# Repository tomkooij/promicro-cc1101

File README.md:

# e07-900m10s adapter board for Arduino Pro Micro (and esp32c3)
Adapter board for [ebyte e07-900m10s CC1101 module](https://www.ebyte.com/en/product-view-news.html?id=1567) and Arduino Pro Micro.

Using [evofw3](https://github.com/ghoti/evofw3) this is an Honeywell HGI-80 clone, that can be used to control Itho/Orcon fans (and evohome devices).
Use the [ramses_cc](https://github.com/zxdavb/ramses_cc) Home Assitant integration.

 - Arduino Pro Micro: mount the reset switch. The RX/TX LEDs are not used: The Pro Micro has on-board leds that are used by evofe3.
 - ESP32-C3: Optionally mount the RX/TX leds. Reset button is on-board. This can run ramses ESP.

TODO (improve in next version):
 - esp32c3 mosi/sclk/miso is reversed as compared my other boards MOSI = 10, SCLK 9... GPO2 5
   (pcb silkscreen is correct)
 - pro micro GND pins next to TX/RX are not connected to pcb GND plane

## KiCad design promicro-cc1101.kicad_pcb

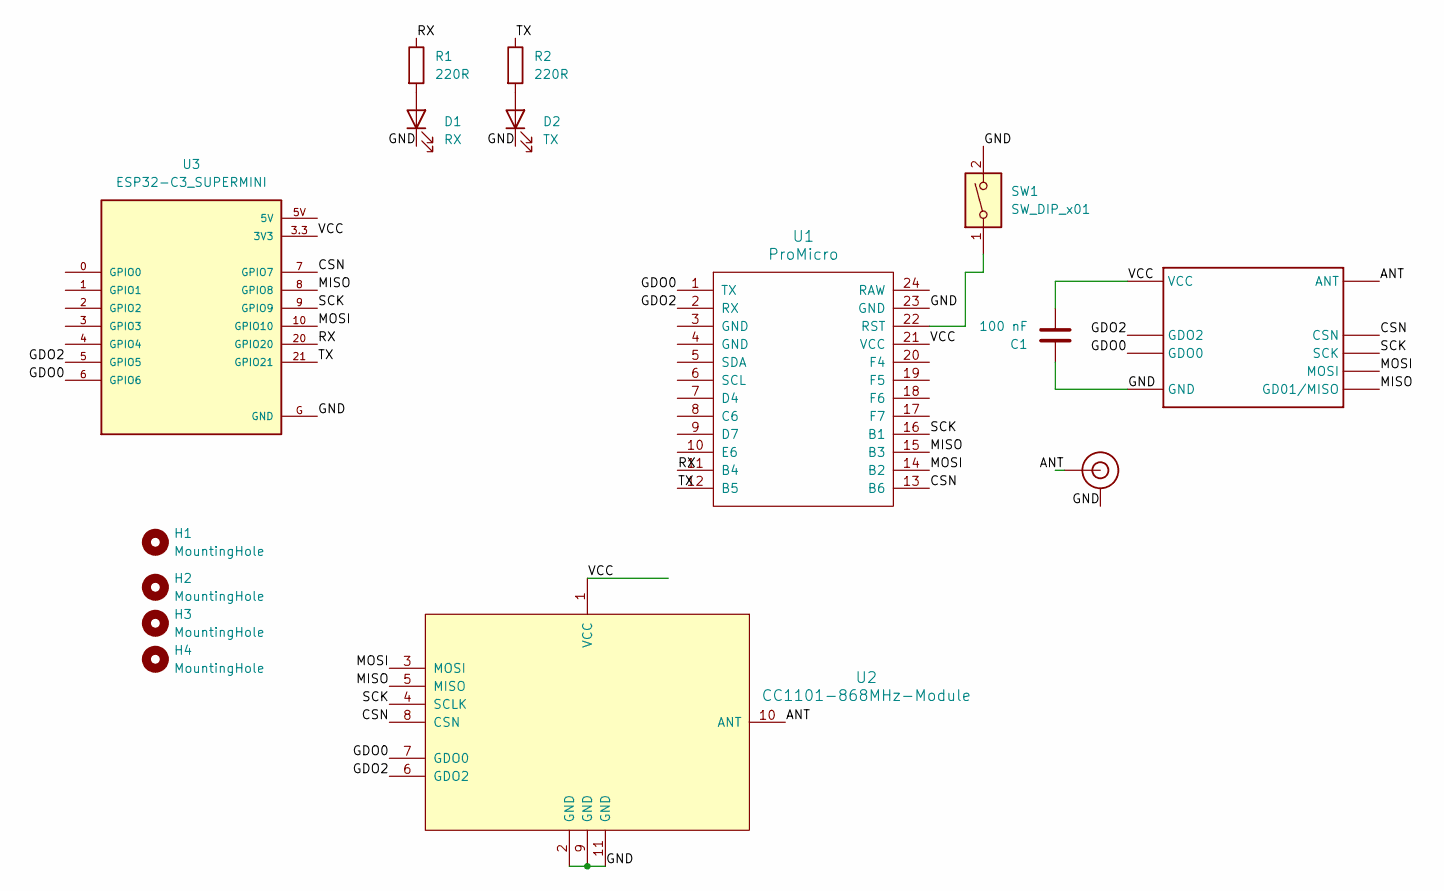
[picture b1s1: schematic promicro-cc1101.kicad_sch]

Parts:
1: E07-900M10S
C1: 100 nF; C_1206_3216Metric_Pad1.33x1.80mm_HandSolder
D1: RX; LED_1206_3216Metric_Pad1.42x1.75mm_HandSolder
D2: TX; LED_1206_3216Metric_Pad1.42x1.75mm_HandSolder
H1, H2, H3, H4: MountingHole; MountingHole_3.2mm_M3
J$1: SMA_PAD
R1, R2: 220R; R_1206_3216Metric_Pad1.30x1.75mm_HandSolder
SW1: SW_DIP_x01; SW_Push_1P1T_NO_CK_KMR2
U1: ProMicro
U2: CC1101-868MHz-Module
U3: ESP32-C3_SUPERMINI; MODULE_ESP32-C3_SUPERMINI

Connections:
/ANT: 1.21 (ANT), J$1.ANT0 (ANT), J$1.ANT1 (ANT), J$1.ANT2 (ANT), U2.10 (ANT)
/CSN: 1.19 (CSN), U1.13 (B6), U2.8 (CSN), U3.7 (GPIO7)
/GDO0: 1.15 (GDO0), U1.1 (TX), U2.7 (GDO0), U3.6 (GPIO6)
/GDO2: 1.14 (GDO2), U1.2 (RX), U2.6 (GDO2), U3.5 (GPIO5)
/GND: 1.1 (GND), 1.2 (GND), 1.3 (GND), 1.4 (GND), 1.5 (GND), 1.11 (GND), 1.12 (GND), 1.20 (GND), 1.22 (GND), C1.1, D1.1 (K), D2.1 (K), J$1.GND3 (GND), J$1.GND4 (GND), J$1.GND5 (GND), J$1.GND6 (GND), SW1.2, U1.23 (GND), U2.2 (GND), U2.9 (GND), U2.11 (GND), U3.G (GND)
/MISO: 1.16 (GD01/MISO), U1.15 (B3), U2.5 (MISO), U3.8 (GPIO8)
/MOSI: 1.17 (MOSI), U1.14 (B2), U2.3 (MOSI), U3.10 (GPIO10)
/RX: R1.1, U1.11 (B4), U3.20 (GPIO20)
/SCK: 1.18 (SCK), U1.16 (B1), U2.4 (SCLK), U3.9 (GPIO9)
/TX: R2.1, U1.12 (B5), U3.21 (GPIO21)
/VCC: 1.9 (VCC), C1.2, U1.21 (VCC), U2.1 (VCC), U3.3.3 (3V3)
unnamed: D1.2 (A), R1.2
unnamed: D2.2 (A), R2.2
unnamed: SW1.1, U1.22 (RST)

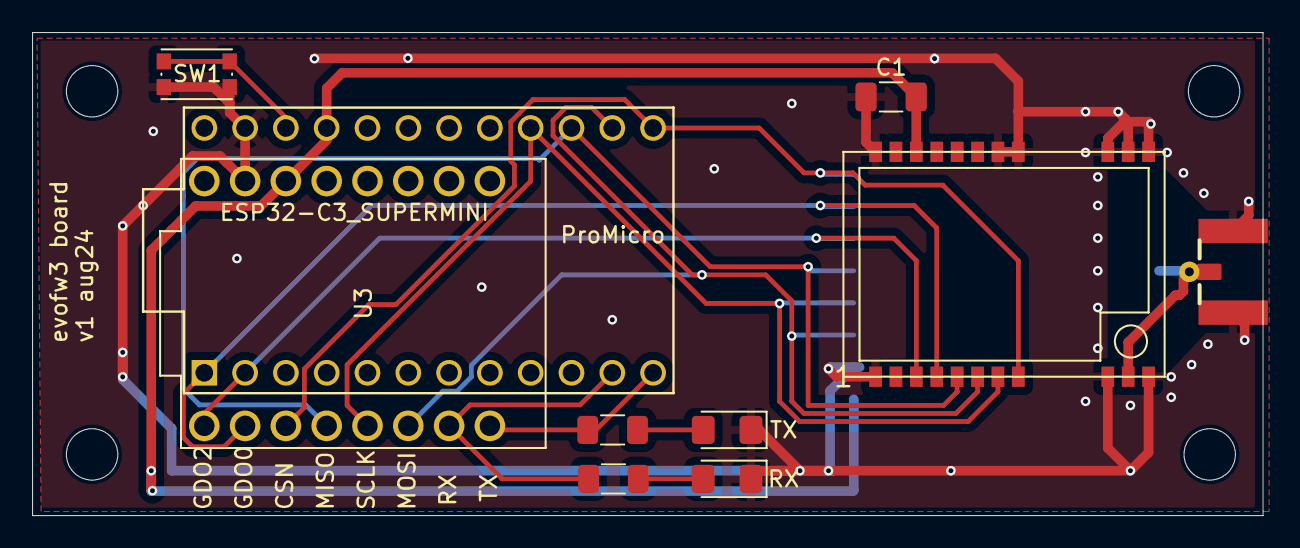
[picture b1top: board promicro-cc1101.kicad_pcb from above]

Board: 2 copper layers, 76.6 x 30.1 mm, 15 parts (1 on the bottom side), 14 nets.

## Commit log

2024-10-17 Add readme
2024-10-26 Add pic of esp32c3 on pcb
